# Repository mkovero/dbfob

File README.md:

# dbfob

**A dirt-cheap keyfob that tells you how loud it is — and how long your ears can take it.**

Double-click the button, look at the colour. Green means you're fine. Red means leave.

dbfob is an open-hardware sound level indicator sized for a keyring. It exists because nobody pulls out a phone on a dark dance floor to run a sound level meter, but everybody can glance at an LED. It is meant to be cheap enough that a venue, a festival or a hearing-health campaign can hand them out at the door next to the free earplugs.

> **Disclaimer:** dbfob is a hobby project, not a calibrated sound level meter or a medical device. Its readings and dose estimates can be wrong, so don't rely on it to protect your hearing. Use your own judgement: if it feels loud, wear earplugs or step away. If you're worried about your hearing, see a professional.

## Status

**Rev A prototype: boards up and measuring. Calibration at loud levels is not done yet. Rev B (B1, an AAA stick with NFC) arrived 2026-11-26 and its first board passes bring-up.**

| Part | State |
|---|---|
| [Hardware](hardware/README.md) | 5 assembled boards from JLCPCB, arrived 2026-10-12. Three are running, with no assembly faults so far. Standby measures 8.2 µA ([bring-up log](hardware/README.md#bring-up-log)). |
| [Firmware](firmware/README.md) | Spot check and dosimeter both work: PDM capture, A-weighting, LAeq, dose, and a flash log of the last dosimeter run (40 % CPU, no overruns). At about 61 dBA it reads within 0.5 dB of a consumer meter. The quiet-room floor is about 48 dBA, which doesn't matter for the bands. |
| [Case](hardware/case/README.md) | Two-shell case, in SLA and FDM builds. The FDM build is printed; a fit check with a board is due this week. |
| [Rev B board B1](hardware/b1/README.md) | 5 assembled boards from JLCPCB, arrived 2026-11-26: a 10.5 × 78.5 mm stick with one AAA cell on the back, a boost converter, a CH32L103, a new mic and an NFC tag. Board 1 passes every block tested so far ([bring-up](hardware/b1/README.md#bring-up)): it runs and starts from 0.57 V, Standby is 19 µA at 1.5 V, the button wakes it, the mic hears, and a phone reads the tag from a couple of centimetres once the antenna is trimmed (22 pF). It has only bring-up test firmware, the metering firmware is not ported yet. Not done: the cell contacts (it has run from a bench supply only), the wake by a phone tap, supply ripple, boards 2–5, a case. |

Next steps: confirm a full 12 h dosimeter night, then calibrate at 85–105 dBA against a reference meter. On rev B: fit the cell contacts, finish the bring-up and port the firmware. See [Next](#next).

## How it works

1. Double-click the button. The fob wakes from standby. A single press, such as one in a pocket, is ignored.
2. A PDM MEMS microphone samples the room for 3 seconds. Meanwhile the LED bar fills up, so you know the press registered and when the answer is coming.
3. The firmware A-weights the signal and computes the equivalent continuous level (LAeq).
4. A four-LED bar shows two verdicts for 2 seconds: a steady LED for a bare ear and a blinking LED for ear plugs. See below.

The LEDs are deliberately dim, since clubs are dark, and they auto-dim using one LED as a light sensor. The light thresholds are not tuned yet. Each reading is also printed on a UART pad for calibration.

### Colour bands

The bands are **levels at the ear**, not safety guarantees. The times are the full daily allowance at that level under the NIOSH / EU occupational curve, `T = 8 h × 2^((85 − L)/3)`: 85 dBA for 8 hours, 3 dB exchange rate.

| Colour | At the ear (dBA) | Daily allowance at that level |
|---|---|---|
| Green | ≤ 83 | Below the 85 dBA / 8 h limit |
| Yellow | 84–90 | About 10 h down to 2.5 h |
| Orange | 91–96 | About 2 h down to 40 min |
| Red | ≥ 97 | Under about 30 min |

A 3-second spot reading describes the room right now, not your night. The allowance is for a whole day starting from zero, so anything you've already heard today uses part of it. Green means this level is below the limit, not that the whole night is safe.

### Two LEDs, two questions

Every reading answers two questions at once, so there is no mode to set or forget:

- **Steady LED: what reaches a bare ear.** This is the room level itself: measured, with no assumptions.
- **Blinking LED: what would reach the ear through plugs that really give 12 dB.** This is a conditional estimate, not a measurement and not a safety verdict. The fob cannot know how well your plugs fit. Foam plugs claim 30+ dB on the box, but inserted in a hurry by someone who's had a drink, 10–15 dB is realistic. A badly seated plug can give much less. Individual fit testing is the only way to know your own attenuation, and NIOSH recommends it.

In a 100 dBA room, red glows steady and yellow blinks: you're in the red, and well-fitted plugs could bring you to yellow. When both answers are the same, only one steady LED lights.

The obvious alternative was a mode switch, but either default misleads someone. Assume plugs, and people without them get a falsely reassuring answer. Assume no plugs, and people who do wear them always see red, so the device looks useless to the people doing the right thing. Showing both removes the default, and the gap between the two LEDs is itself the argument for plugs.

### Modes

- **Double click — spot check.** Measures the current level and shows a colour for a few seconds. This is the mode that is always trustworthy, because you are holding the device out in front of you.
- **Long press (2 s) — dosimeter.** *Works on the bench. A 9 h run averaged 165 µA at 3.0 V: about 2 mAh per 12 h night, or roughly 80 nights on a CR2032. The first full 12 h runs, ending in auto-off, are in progress.*
  - **Start:** the LEDs light up and flash twice to confirm.
  - **While running:** the fob wakes about every 30 s and samples for 1 s about once a minute, with the LEDs off.
  - **Triple click:** shows the dose so far, bare ear, as a share of the daily allowance. The whole bar blinks for 3 s, and the faster it blinks, the more of the allowance is used: once a second at 0 %, twice a second at 50 %, and steadily lit at 100 %. A single click does nothing, so a press in a pocket doesn't light the fob.

  - **Stop:** another long press. The bar empties from red to green.
  - **Auto-off:** after 12 h it stops by itself. A triple click still shows the final dose until the next start.
  - **Double click:** a spot check, which works as usual while the dosimeter runs.
  - **Log:** the latest run, with about one level per minute, stays in flash after the cell is removed. You can read it later through the programmer with `make dose-log` (see [firmware/README.md](firmware/README.md)).

The catch is that a keyfob lives in a pocket. A pocket reads 10–20 dB low with the high end rolled off, so a dose collected in a pocket is a comforting lie. The dosimeter doesn't yet detect this. It would need to from the spectrum, since the high-band to low-band energy ratio collapses in a pocket, and then refuse to count those samples and flag the dose as incomplete. For now, clip it to your shoulder or a bag strap, with the mic port uncovered.

#### Example night

This is the flash log from one fob over a full 12 h run that ended in auto-off. The fob took 643 samples, all valid. It read with `make dose-log`, and the graph was drawn with `tools/dose_log.py --svg`:

- **Quiet room, 0–2.3 h:** the fob reads its own floor, about 48 dBA.
- **Music, 2.3–6.3 h:** 55–75 dBA. Hours of this barely move the dose.
- **Drums, 6.4 h:** ten minutes at 85–89.5 dBA. That alone takes the dose from about 0.5 % to 2.9 %, because each 3 dB doubles the rate.
- **Walk home, 9.8 h:** up to 80 dBA, with the fob in a pocket. Street noise would have read louder in the open, so this part of the dose is understated: the pocket problem described above.
- **Total:** LAeq 68.1 dBA over 12 h, which is 3.1 % of the daily allowance. A triple click would have shown the slowest blink, about once a second.

A cased and a bare fob side by side through a night in front of a big PA: [docs/logs/2026-10-31-case-ab.md](docs/logs/2026-10-31-case-ab.md).

## Hardware

This section describes rev A. Rev B's parts are in [hardware/b1](hardware/b1/README.md).

No radio, no display, no app. The design goal was **under €2 all-in**. The rev A parts come to about $1.85 per board at 1,000 units. A 130 dB-capable mic alone is about €1.2, so sub-€1 is out unless mic prices drop.

| Block | Part | Why |
|---|---|---|
| Microphone | Infineon **IM69D130**, PDM | **Acoustic overload ≥ 130 dB SPL.** Hobby-favourite digital mics clip at about 120 dB, which a club sub stack exceeds. It is digital, with ±1 dB sensitivity, so a batch can be calibrated rather than each unit, and the reading doesn't drift with battery voltage. |
| MCU | WCH **CH32V003F4P6** | The CH32V002/V006 are pin-compatible drop-ins, but were out of stock. The V003 has no hardware multiplier (handled in firmware) and needs at least 2.7 V. |
| LEDs | 4 × 0603 low-Vf LEDs as a bar: yellow-green, yellow, orange, red | InGaN green and blue LEDs need about 3 V and fade on a coin cell. The bar position also encodes the level for colour-blind users. D4 doubles as the light sensor. |
| Power | CR2032 in a Keystone 3034 | Standby measures 8.2 µA, so an idle fob lasts about 3 years. The mic is powered only while measuring. The dosimeter averages about 165 µA. |
| Input | 1 × tactile switch | Wakes the MCU. |
| Case | 3D-printed two-part shell, one M2 screw | Mic and LEDs at one end, keyring at the other. |

Background and trade-offs:
- The part comparison is in [docs/mic-mcu-options.md](docs/mic-mcu-options.md).
- An independent hardware audit, with the response to each finding, is in [docs/hardware-audit-2026-09-27.md](docs/hardware-audit-2026-09-27.md).

### Accuracy

Cheap MEMS parts are ±3 dB sensitivity; better ones are ±1 dB and factory-calibrated. Either is fine for four colour bands. The real uncertainty in this device is placement (held out vs. cupped in a hand vs. in a pocket) and earplug fit, not the microphone. Design effort goes into making "not trustworthy" visible, not into the last dB.

### Calibration

A 94 dB pistonphone won't couple to a MEMS port. Calibrate by substitution instead: place the fob next to a measurement mic in a room with pink noise at a few levels, note the offset, store it in flash. Also characterise the offset when hand-held vs. on a table, since that is how people will actually use it.

## Repository layout

```
hardware/        KiCad project, generated from the tables in hardware/tools/ (schematic, PCB, JLC outputs)
hardware/case/   FreeCAD case script, STEP/STL for printing, board geometry it is built from
hardware/b1/     rev B board (AAA stick, CH32L103, NFC tag): KiCad project, JLC outputs, bring-up log
firmware/        CH32V003 firmware on ch32fun: PDM capture, A-weighting, LAeq, LEDs, standby, dosimeter and its
                 flash log (tools/dose_log.py decodes it); host tests
firmware/b1-*/   rev B bring-up tests for the CH32L103: b1-test (LEDs, button, supply, tag, mic),
                 b1-standby (sleep current), b1-fd (wake by a phone's field)
docs/            part selection, hardware audit, log readout ideas
```

## Next

- [x] First bring-up: power, programming, mic capture, CPU load.
- [x] Standby current (8.2 µA) and the dosimeter current profile.
- [ ] VDD reference trim, light-sense thresholds. See [firmware/README.md](firmware/README.md#bring-up-checklist).
- [ ] Calibrate against a reference meter at 85–105 dBA, in the case: the level offset and the hand-held offset. So far it has only been compared with a consumer meter at about 61 dBA.
- [ ] Qualify the battery: the supply voltage under load across cell charge and temperature, then set the cutoff. At 2.8 V the sample wakes read 25 % more current than at 3.0 V. Re-measure on a range with a smaller burden voltage. A low-battery lockout (2.75 V) now keeps a tired cell from hanging the V003; test it with real cells. Wakes peak at over 10 mA with the LEDs on, which is hard on a CR2032.
- [x] Print the case.
- [ ] Check the printed case: the tolerances, the button flexure and the mic seal.
- [ ] A calibration procedure anyone can repeat with a known-good meter.
- [x] Rev B board designed and ordered: [B1](hardware/b1/README.md), an AAA stick with a boost converter, a CH32L103 (hardware multiplier, runs from 1.8 V), a mic port at the tip and an NFC tag for reading the dose log without a programmer ([directions, checked facts, experiments](docs/rev-b.md); [readout ideas](docs/log-readout.md)).
- [x] Rev B first bring-up on board 1: power from 0.57 V, programming, LEDs, button, Standby (19 µA at 1.5 V), mic, tag and antenna trim ([log](hardware/b1/README.md#bring-up)).
- [ ] Rev B: fit the cell contacts and run from a real AAA; wake by a phone tap; supply ripple at the mic; bring up boards 2–5.
- [ ] Rev B: port the metering firmware to the CH32L103 and the new mic, and write the log to the tag. Full-band A-weighting to 20 kHz is the goal there: rev A stops at 11.7 kHz, which reads only ~0.2–0.9 dB low on broadband noise, but high-frequency content is exactly what a listener stops noticing after a few drinks at a club ([band limit](firmware/README.md#signal-chain)).
- [ ] Rev B: a case for the stick.
- [ ] Dosimeter: confirm the 12 h auto-off and the flash log over a full night, then occlusion (pocket) detection.
- [ ] Get a batch into a venue and see if people use them.

## Non-goals

- Bluetooth, apps, logging to the cloud. The point is that nothing needs to be looked at except one LED.
- Certified measurement accuracy. This is a warning light, not a Class 1 meter.

## Why

Hearing damage is cumulative and irreversible, and the people most at risk are the ones who go out the most. Earplugs are cheap and effective, but people don't put them in unless they have a reason to. A colour that says "you are in the red" is a reason.

## License

Hardware: CERN-OHL-P. Firmware: MIT. Documentation: CC BY 4.0.

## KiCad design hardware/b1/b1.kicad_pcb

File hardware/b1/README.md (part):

# B1 (rev B)

A stick, 10.5 × 78.5 × 1.6 mm, 4 layers, with the mic at the tip and one AAA cell on the back: rev A's metering, with the log readable by tapping a phone. Scope and part choices are in [docs/rev-b.md](../../docs/rev-b.md#b1-stick-aaa-instead-of-cr2032-decided-2026-11-09).

**Status: boards arrived 2026-11-26; board 1 passes bring-up as far as it can go without cell contacts** (see [Bring-up](#bring-up)): supply, MCU, LEDs, button, Standby, mic, and the tag read by a phone after a 22 pF trim. Open: the contacts, FD wake, ripple, boards 2–5. Ordered from JLCPCB on 2026-11-16 (commit e3a0548: 5 boards, 4 layers, 1.6 mm, ENIG, Economic PCBA on the top side, mic SPH0655LM4H-1). Redrawn as the AAA stick on 2026-11-09. The first draft (2026-11-03) was a 30 × 26 mm CR2032 board. The [NFC test board](../nfc-test/README.md) shares its antenna, outline and cell but was dropped from the order on 2026-11-12: B1 finds its own trim (see [On the bench](#on-the-bench-nfc)).

## What's on it

Along the stick from the tip:

- **The tip, 24 mm:** the NFC coil, from [../lib/antenna.py](../lib/antenna.py), shared with the (unordered) test board. It has 9 turns of 0.15 mm track with a 0.15 mm gap, about 2.25 µH in air (NXP AN11276). The mic MK1 sits inside it, with its port through the board, and C6/R8 sit beside it. The coil's inner end meets LB at net tie NT1; LB crosses under the turns on B.Cu.
- **Just past the coil:** the tag U1, trim pads C1/C2 and C3.
- **The middle:** the tag's pull-ups, the LED bar (LED at the top edge, its resistor below, with only the cathode bar in silk; D1 and D2 are 0805, D3 and D4 0603, all four columns on one 1.75 mm pitch, LEDs in one row and resistors in another; the pull-ups and C3 stand 1.05 mm from the tag's body, JLC's spacing for a QFN), then the button SW1 about mid-stick (x 42.3 of 78.5), where a thumb finds it while the far end rests in the hand. Then the Tag-Connect footprint J1, **pads on the back**, under the cell, so a sweaty thumb can't touch them; its guide and clip holes go through the board in the gap between the two contacts' base pads. Then the MCU U2, still in that gap, so its vias have room all round, and right after it the boost converter U3, with L1 over it and C5 under it, so the switching and output loops stay on F.Cu (hand-drawn). It sits over the + contact's base pad: its VCELL via goes into that pad, the rest of its vias above and below it.
- **The far end:** a 2.4 mm round ring hole H1 in the corner, past the + contact's plate, for hanging the stick up. The MY-AAA-07 drawing has no dimension for the plate; scaled from it, the plate's top lip stands 1.4 mm inboard of the foot's tip, which puts it at x 74.2 to 74.5 depending on where the contact sits on its pads, with about 0.4 mm of scaling and part tolerance on top. The hole starts at x 75.2 and is as big as the corner allows: 0.9 mm of web to the end and to the side, 0.72 mm to the contact's foot pad (a hole counts as board edge). The board is 2 mm longer than the first B1 draft to make room. Solder the + contact towards the mic end of its pads, and check the gap with a real one. The board's name is on the back silk, under the coil.
- **Back:** the AAA cell between two MYOUNG MY-AAA-07 spring contacts, hand-fitted, + towards the far end. Other nets' vias keep at least 0.35 mm from the contacts' pads (the pads are grown while routing), so hand-soldering has room. Everything past the coil sits under the cell.
- **No planes or pours on any layer.** Copper near the loop detunes it, so GND is tracks. Every layer under the coil is kept clear, apart from a band at its cell end where LB and the mic's nets cross under the turns.

**Why 4 layers:** two would not route in 10.5 mm. The MCU's fan-out, the tag's lines and the mic's lines share one corridor, and the contacts' pads fill the middle of B.Cu. The inner layers carry signals only.

| Ref | What | Note |
|---|---|---|
| U2 | CH32L103F8U6, C22467836 | QFN-20 3 × 3. No NRST pin, BOOT0 tied low inside |
| U3 | TLV61220DBVR, C111811 | boost, 0.7 V start-up, 3.0 V out (R9 1 MΩ / R10 200 kΩ); EN to the cell, always on |
| L1 | MPL2016S4R7MHT, C98335 | 4.7 µH, 2.0 × 1.6 mm, multilayer |
| C5, C7 | 10 µF | boost output, input |
| MK1 | Knowles SPH0655LM4H-1, C22376158 | 132.5 dB SPL AOP, −37 ±1 dBFS, normal mode 1.1–4.8 MHz (below 0.9 MHz it drops to low-power mode, 116 dB AOP: keep the clock at 1.5 MHz). 0.6 mm port (NPTH) through the board, inside the coil. Replaces the IM66D130M, which JLC assembles only as Standard PCBA |
| R8, C6 | 100 Ω, 1 µF (C15849) | mic supply from PA4, filtered against the boost's burst ripple |
| U1 | NT3H2111W0FHKH, C710403 | NTAG I2C plus 1k, powered from PB14 |
| C1, C2 | 0603 trim, **not fitted** | C0G, value found on the bench: 22 pF in C1 on board 1 (see Bring-up) |
| C3, C4 | 100 nF | tag and MCU decoupling |
| R1, R2 | 4.7 kΩ, 0402 (C25900) | SDA / SCL pull-ups to NFC_VCC. 0402 to make room for the 0805 LEDs |
| R3 | 100 kΩ, 0402 (C25741) | FD pull-up to VDD |
| R11 | 4.7 kΩ, 0402 (C25900) | in series with PA7's cell sense |
| D1–D4, R4–R7 | green KT-0805G (C2297), yellow KT-0805Y (C2296), red KT-0603R (C2286) ×2; 1 kΩ, 2.2 kΩ ×3 | **All JLC basic parts** (no extended fee), which is why the bar is green, yellow, red, red: basic has no orange, and green and yellow only in 0805. The green is InGaN (2.6–3.1 V at 5 mA) on the 3.0 V rail: dim by design, tune R4 on the bench. Each on its own hardware PWM channel; D4's cathode on PA10 for ambient-light sensing. D3's net is still called LED_O |
| SW1 | TS-1187A, C318884 | measure button, PA0/WKUP to VDD: no resistor |
| BT1 | 2 × MY-AAA-07 (C6937109) | **hand-fit on the back**, so JLC assembly stays one-sided |
| H1 | 2.4 mm NPTH | ring / cord hole in the far corner; a light split ring is fine, but a heavy key bunch should hang from the case |
| J1 | Tag-Connect TC2050-IDC footprint (KiCad stock `TC2050-IDC-FP`, for the legged plug), no part | 2 × 5 pogo pads at 1.27 mm, 3 guide holes and 4 clip holes (2.4 mm), **on the back**, along the stick between the button and the MCU, its holes in the gap between the contacts' base pads, 0.4 mm clear of the button's body on the front, where the clips latch. ARM Cortex 10-pin pinout: 1 VDD (VTref), 2 SWDIO, 4 SWCLK, 6 TX (SWO slot: the dB stream), 3/5/9 GND; 7, 8, 10 not connected (no NRST pin) |

**MCU pins** (full table in `tools/gen_sch.py`):

| Pin | Net | | Pin | Net |
|---|---|---|---|---|
| 1 PA0 | BTN (WKUP: wakes Standby on a rising edge) | | 7 PA7 | VCELL (ADC7: the cell, for the low-battery lockout) |
| 2 PA1 | LED_O (TIM2_CH2) | | 8 PB0 | FD (EXTI) |
| 3 PA2 | LED_Y (TIM2_CH3) | | 9 PB10 | SCL (I2C2) |
| 4 PA3 | LED_G (TIM2_CH4) | | 10 PB11 | SDA (I2C2) |
| 14 PA8 | LED_R (TIM1_CH1) | | 12 PB14 | NFC_VCC |
| 18 PA10 | LED_R_K | | 15 PA9 | TX (USART1) |
| 5 PA4 | MIC_PWR (through R8 to MIC_VDD) | | 17 PA13 | SWDIO |
| 6 PA5 | MIC_CLK (SPI1 SCK) | | 16 PA14 | SWCLK |
| 20 PA6 | MIC_DATA (SPI1 MISO) | | 11, 13 | spare (PB13, PB15) |

- **Button on WKUP.** With EWUP set, PA0 is forced to an input with pull-down in Standby, so the button goes to VDD and needs no resistor. Not PB13: it shares a pad with PB6 = CC1, and some lots force CC1's 5.1 kΩ pull-down on in Standby (datasheet table 3-8-1 note 3). For the same reason NFC_VCC is on PB14, not PB13.
- Pins sharing a pad inside the chip (PB1/PB10, PA10/PB7, PA11/PA13, PA12/PA14): only one of each pair may drive. Keep CC2_PD off, or PA10 gets 5.1 kΩ to ground.
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
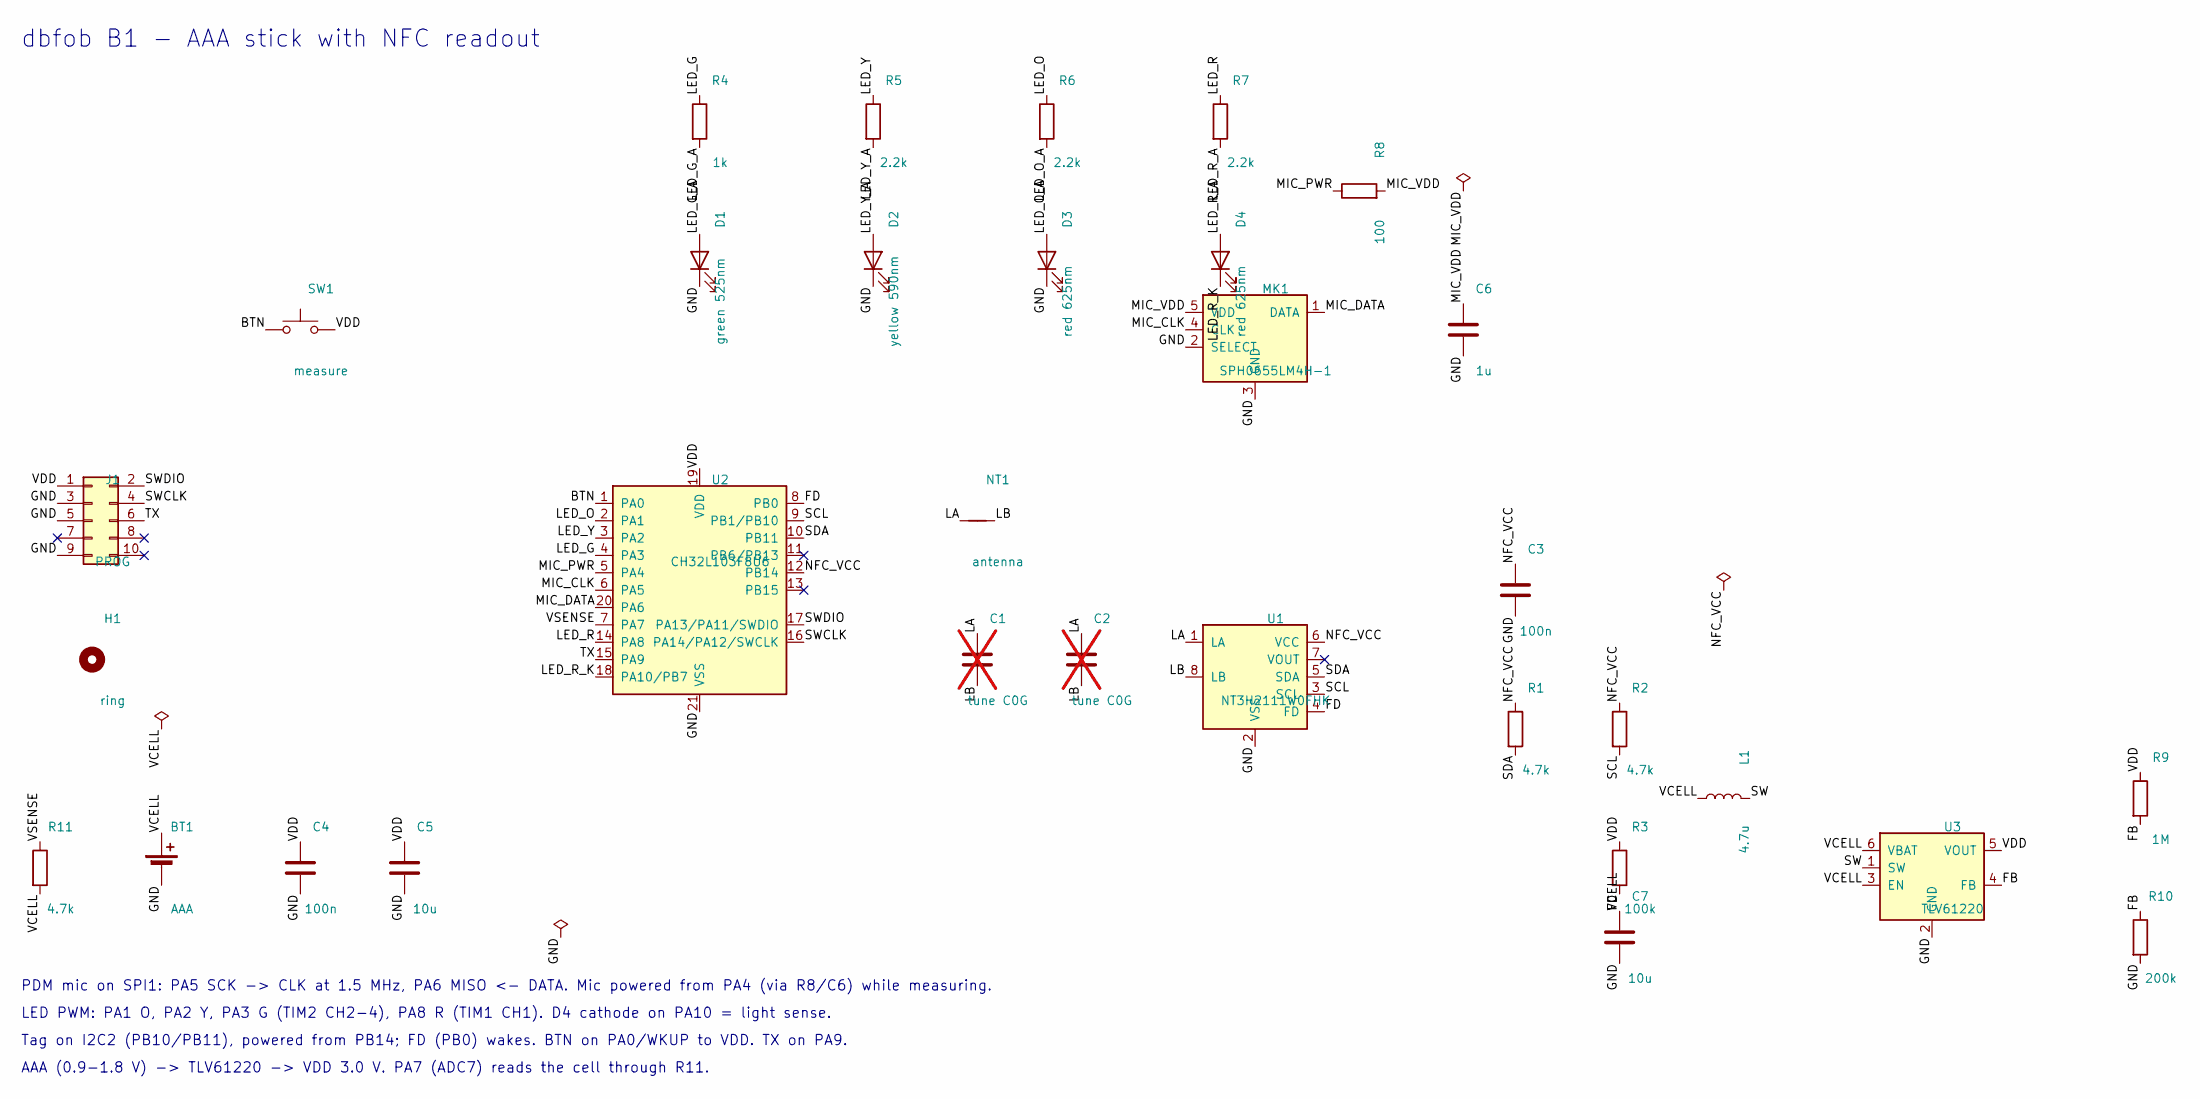
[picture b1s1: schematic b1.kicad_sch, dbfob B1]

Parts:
BT1: AAA; BatteryContacts_MYOUNG_MY-AAA-07_1xAAA; MPN MY-AAA-07
C1, C2: tune C0G; C_0603_1608Metric; not fitted
C3, C4: 100n; C_0603_1608Metric; MPN CC0603KRX7R9BB104; LCSC C14663
C5, C7: 10u; C_0603_1608Metric; MPN CL10A106KP8NNNC; LCSC C19702
C6: 1u; C_0603_1608Metric; MPN CL10A105KB8NNNC; LCSC C15849
D1: green 525nm; LED_0805_2012Metric_narrow; MPN KT-0805G; LCSC C2297
D2: yellow 590nm; LED_0805_2012Metric_narrow; MPN KT-0805Y; LCSC C2296
D3, D4: red 625nm; LED_0603_1608Metric; MPN KT-0603R; LCSC C2286
H1: ring; RingHole_2.4mm
J1: PROG; Tag-Connect_TC2050-IDC-FP_2x05_P1.27mm_Vertical
L1: 4.7u; L_0806_2016Metric_MPL2016; MPN MPL2016S4R7MHT; LCSC C98335
MK1: SPH0655LM4H-1; Knowles_SPH0655LM4H_LGA-5_3.5x2.65mm; MPN SPH0655LM4H-1-8; LCSC C22376158
NT1: antenna; NetTie-2_SMD_Pad0.5mm
R1, R2, R11: 4.7k; R_0402_1005Metric; MPN 0402WGF4701TCE; LCSC C25900
R3: 100k; R_0402_1005Metric; MPN 0402WGF1003TCE; LCSC C25741
R4: 1k; R_0603_1608Metric; LCSC C21190
R5, R6, R7: 2.2k; R_0603_1608Metric; LCSC C4190
R8: 100; R_0603_1608Metric; MPN 0603WAF1000T5E; LCSC C22775
R9: 1M; R_0603_1608Metric; MPN 0603WAF1004T5E; LCSC C22935
R10: 200k; R_0603_1608Metric; MPN 0603WAF2003T5E; LCSC C25811
SW1: measure; SW_Push_1P1T_XKB_TS-1187A; MPN TS-1187A-B-A-B; LCSC C318884
U1: NT3H2111W0FHK; NXP_XQFN-8_1.6x1.6mm_P0.5mm; MPN NT3H2111W0FHKH; LCSC C710403
U2: CH32L103F8U6; UQFN-20-1EP_3x3mm_P0.4mm_EP1.85x1.85mm; MPN CH32L103F8U6; LCSC C22467836
U3: TLV61220; SOT-23-6; MPN TLV61220DBVR; LCSC C111811

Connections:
/BTN: SW1.1, U2.1 (PA0)
/FB: R9.2, R10.1, U3.4 (FB)
/FD: R3.2, U1.4 (FD), U2.8 (PB0)
/GND: BT1.2 (-), C3.2, C4.2, C5.2, C6.2, C7.2, D1.1 (K), D2.1 (K), D3.1 (K), J1.3, J1.5, J1.9, MK1.2 (SELECT), MK1.3 (GND), R10.2, U1.2 (VSS), U2.21 (VSS), U3.2 (GND)
/LA: C1.1, C2.1, NT1.1, U1.1 (LA)
/LB: C1.2, C2.2, NT1.2, U1.8 (LB)
/LED_G: R4.1, U2.4 (PA3)
/LED_G_A: D1.2 (A), R4.2
/LED_O: R6.1, U2.2 (PA1)
/LED_O_A: D3.2 (A), R6.2
/LED_R: R7.1, U2.14 (PA8)
/LED_R_A: D4.2 (A), R7.2
/LED_R_K: D4.1 (K), U2.18 (PA10/PB7)
/LED_Y: R5.1, U2.3 (PA2)
/LED_Y_A: D2.2 (A), R5.2
/MIC_CLK: MK1.4 (CLK), U2.6 (PA5)
/MIC_DATA: MK1.1 (DATA), U2.20 (PA6)
/MIC_PWR: R8.1, U2.5 (PA4)
/MIC_VDD: C6.1, MK1.5 (VDD), R8.2
/NFC_VCC: C3.1, R1.1, R2.1, U1.6 (VCC), U2.12 (PB14)
/SCL: R2.2, U1.3 (SCL), U2.9 (PB1/PB10)
/SDA: R1.2, U1.5 (SDA), U2.10 (PB11)
/SW: L1.2, U3.1 (SW)
/SWCLK: J1.4, U2.16 (PA14/PA12/SWCLK)
/SWDIO: J1.2, U2.17 (PA13/PA11/SWDIO)
/TX: J1.6, U2.15 (PA9)
/VCELL: BT1.1 (+), C7.1, L1.1, R11.2, U3.3 (EN), U3.6 (VBAT)
/VDD: C4.1, C5.1, J1.1, R3.1, R9.1, SW1.2, U2.19 (VDD), U3.5 (VOUT)
/VSENSE: R11.1, U2.7 (PA7)

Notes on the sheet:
dbfob B1 - AAA stick with NFC readout
PDM mic on SPI1: PA5 SCK -> CLK at 1.5 MHz, PA6 MISO <- DATA. Mic powered from PA4 (via R8/C6) while measuring.
LED PWM: PA1 O, PA2 Y, PA3 G (TIM2 CH2-4), PA8 R (TIM1 CH1). D4 cathode on PA10 = light sense.
Tag on I2C2 (PB10/PB11), powered from PB14; FD (PB0) wakes. BTN on PA0/WKUP to VDD. TX on PA9.
AAA (0.9-1.8 V) -> TLV61220 -> VDD 3.0 V. PA7 (ADC7) reads the cell through R11.

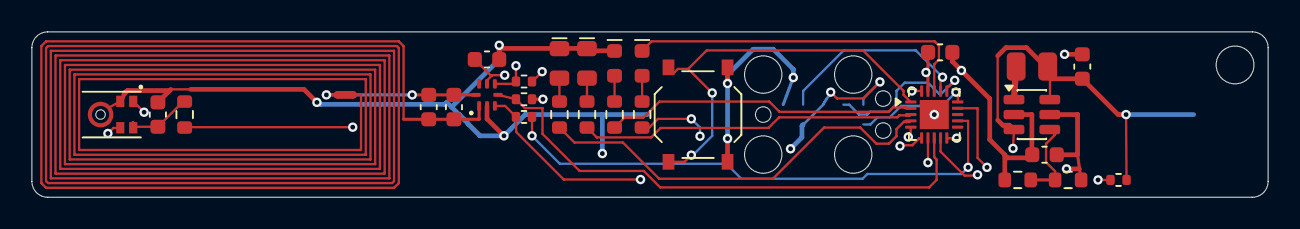
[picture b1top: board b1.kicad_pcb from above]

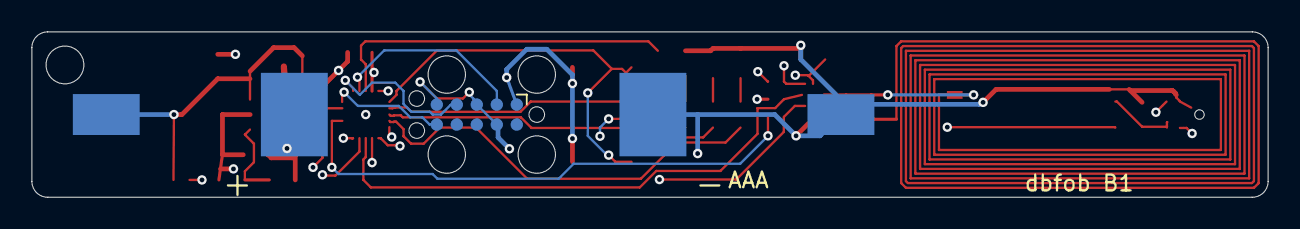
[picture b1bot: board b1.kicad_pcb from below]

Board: 4 copper layers, 78.5 x 10.5 mm, 32 parts (2 on the bottom side), 29 nets.

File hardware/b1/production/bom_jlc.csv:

Comment,Designator,Footprint,LCSC Part #
100n CC0603KRX7R9BB104,"C3,C4",C_0603_1608Metric,C14663
10u CL10A106KP8NNNC,"C5,C7",C_0603_1608Metric,C19702
1u CL10A105KB8NNNC,C6,C_0603_1608Metric,C15849
green 525nm KT-0805G,D1,LED_0805_2012Metric_narrow,C2297
yellow 590nm KT-0805Y,D2,LED_0805_2012Metric_narrow,C2296
red 625nm KT-0603R,"D3,D4",LED_0603_1608Metric,C2286
4.7u MPL2016S4R7MHT,L1,L_0806_2016Metric_MPL2016,C98335
SPH0655LM4H-1 SPH0655LM4H-1-8,MK1,Knowles_SPH0655LM4H_LGA-5_3.5x2.65mm,C22376158
4.7k 0402WGF4701TCE,"R1,R2,R11",R_0402_1005Metric,C25900
100k 0402WGF1003TCE,R3,R_0402_1005Metric,C25741
1k,R4,R_0603_1608Metric,C21190
2.2k,"R5,R6,R7",R_0603_1608Metric,C4190
100 0603WAF1000T5E,R8,R_0603_1608Metric,C22775
1M 0603WAF1004T5E,R9,R_0603_1608Metric,C22935
200k 0603WAF2003T5E,R10,R_0603_1608Metric,C25811
measure TS-1187A-B-A-B,SW1,SW_Push_1P1T_XKB_TS-1187A,C318884
NT3H2111W0FHK NT3H2111W0FHKH,U1,NXP_XQFN-8_1.6x1.6mm_P0.5mm,C710403
CH32L103F8U6 CH32L103F8U6,U2,UQFN-20-1EP_3x3mm_P0.4mm_EP1.85x1.85mm,C22467836
TLV61220 TLV61220DBVR,U3,SOT-23-6,C111811

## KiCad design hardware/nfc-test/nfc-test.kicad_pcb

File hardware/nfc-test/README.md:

# NFC test board (for rev B / B1)

**Dropped on 2026-11-12, not ordered.** Shipped in the same order as B1 it could not steer B1's layout, and B1 answers the same question itself: its tag runs from the phone's field with no firmware, over the same antenna and cell, with its own mic and lines in place (see [B1's bench steps](../b1/README.md#on-the-bench-nfc)). Kept as a draft; it still imports [../lib/antenna.py](../lib/antenna.py) but its board files are not regenerated when that changes.

10.5 × 94 mm as drawn (B1 is now 76.5 mm; rerun make_pcb if this board is ever revived), 1.0 mm thick, 4 layers like B1 (the inner two are empty here, so the coil sees the same stack-up): B1's stick outline. It answers one question before B1 is trusted: **does B1's NFC antenna read on a phone with the AAA cell beside it, and with what trim?** This is [experiment 4](../../docs/rev-b.md#experiments-before-any-board).

It goes in the **same order as B1**, so it can't steer B1's layout. B1 copies this antenna and its trim pads exactly. Whatever trim value this board finds goes straight onto B1's pads.

## What's on it

- **Tip, 24 mm:** B1's antenna block, from [../lib/antenna.py](../lib/antenna.py), which both boards import so they can't drift apart:
  - a 9-turn PCB coil, 0.15 mm track with a 0.15 mm gap, about 23 × 9.3 mm, about 2.25 µH in air (NXP AN11276 formula);
  - its inner end meets LB through net tie NT1; LB drops through a via and crosses under the cell-end turns on B.Cu to the tag;
  - **U1** (NT3H2111, NTAG I2C plus 1k), **C3** and the **C1/C2** trim pads (not fitted) just past the coil, where they sit on B1.
- **Back:** B1's AAA cell between two MYOUNG MY-AAA-07 spring contacts, its near end about 1.4 mm past the coil. The cell is there for its steel can. At 1.5 V it can't run the tag (1.67 V minimum) or the LED.
- **Past the tag:** the pull-ups where B1 has them, the D1 field LED, and six host pads.

| Ref | What | Note |
|---|---|---|
| U1 | NT3H2111W0FHKH, C710403 | VOUT unused |
| C1, C2 | 0603 trim, **not fitted** | C0G, chosen on the bench |
| C3 | 100 nF | VCC decoupling |
| R1, R2 | 4.7 kΩ | SDA / SCL pull-ups to VCC |
| R3 | 10 kΩ | FD pull-up to VCC |
| R4, D1 | 1 kΩ, red | lit while a reader's field is on and VCC is up: FD pulls it low |
| BT1 | 2 × MY-AAA-07 (C6937109) | **hand-fit on the back**, so JLC assembly stays one-sided |
| J1 | 6 SMD pads, 2.54 mm | `G C F D V B` = GND, SCL, FD, SDA, VCC, VCELL; for wires or pogo pins |

## Regenerate

```sh
python3 hardware/lib/gen_lib.py               # NT3H2111 symbol, XQFN8 + AAA contact footprints
python3 hardware/nfc-test/tools/gen_sch.py    # tables -> schematic
python3 hardware/nfc-test/tools/make_pcb.py   # coil + placement + hand-drawn LA/LB, the router does the rest
python3 hardware/nfc-test/tools/fab.py        # -> production/
```

This follows the same procedure as rev A ([../README.md](../README.md)).

**How the antenna is drawn.** The coil is LA track; its outer end runs straight to the tag's LA pin. Its inner end meets LB through net tie NT1, and LB crosses under the turns on B.Cu (VI to VO). DRC doesn't check clearance within one net, so `antenna.py` builds the turns at a fixed pitch and asserts the 0.15 mm gap, and the vias' gap to the turns, itself.

**State at commit:**
- **ERC:** clean, apart from the library-table warnings.
- **DRC:** 0 errors, 0 unconnected, 0 parity issues.
- **Repeatability:** two runs give byte-identical boards.
- **CPL:** all 7 placements checked against JLC's EasyEDA footprints.

## On the bench

Power the tag side from a 3 V supply on V and G (or a host MCU, which also gets C, D and F) so D1 can show the field.

1. **No cell.** Tap with an Android (NXP TagInfo) and an iPhone. Write a URL with NFC Tools. Note the read distance, and the distance at which D1 lights.
2. **Find the resonance**, if a NanoVNA and a small pickup loop are at hand. Couple the loop loosely and read the S11 dip, f0. Then the trim is **C = 50 pF × ((f0 / 13.56 MHz)² − 1)**. Without a VNA, try 0, 4.7, 10, 15 and 22 pF C0G in C1, and keep the value with the longest read distance.
3. **Fit the cell** (an alkaline and, if B1 will take one, a lithium AAA). Repeat steps 1–2. This shows how much the cell costs.
4. **In the case**, if one is printed: repeat steps 1–2 with the board in it.
5. **Locked iPhone:** with the screen on, a tap should open the URL with no app.

Record f0, the trim value, the read distance and the LED distance for each step. The trim value from step 3 (or 4) goes on B1's pads.

**Why the coil is under 2.75 µH.** 13.56 MHz needs 2.75 µH with the tag's 50 pF (44–56 pF). The coil is short of that on purpose: the cell, its contacts and a phone pull the tuning about, and a parallel trim cap can only pull the resonance down.

**What it doesn't copy.** The coil, LA/LB, tag, trim pads, outline, stack-up and cell are B1's exactly. B1's Tag-Connect footprint (about 18 mm from the coil), MCU and boost converter, and its mic and lines are not: the mic's lid sits inside the coil, with two 11 mm tracks beside it, a 12 mm GND track under it, and four more nets crossing under the turns at the cell end. The cell's steel can is the bigger effect, but check B1's resonance again (VNA, step 2) before its C1/C2 value is final.

**Ordering note:** In1 and In2 are empty on purpose (same stack-up as B1). JLC may ask about blank inner layers on a 4-layer order: confirm.

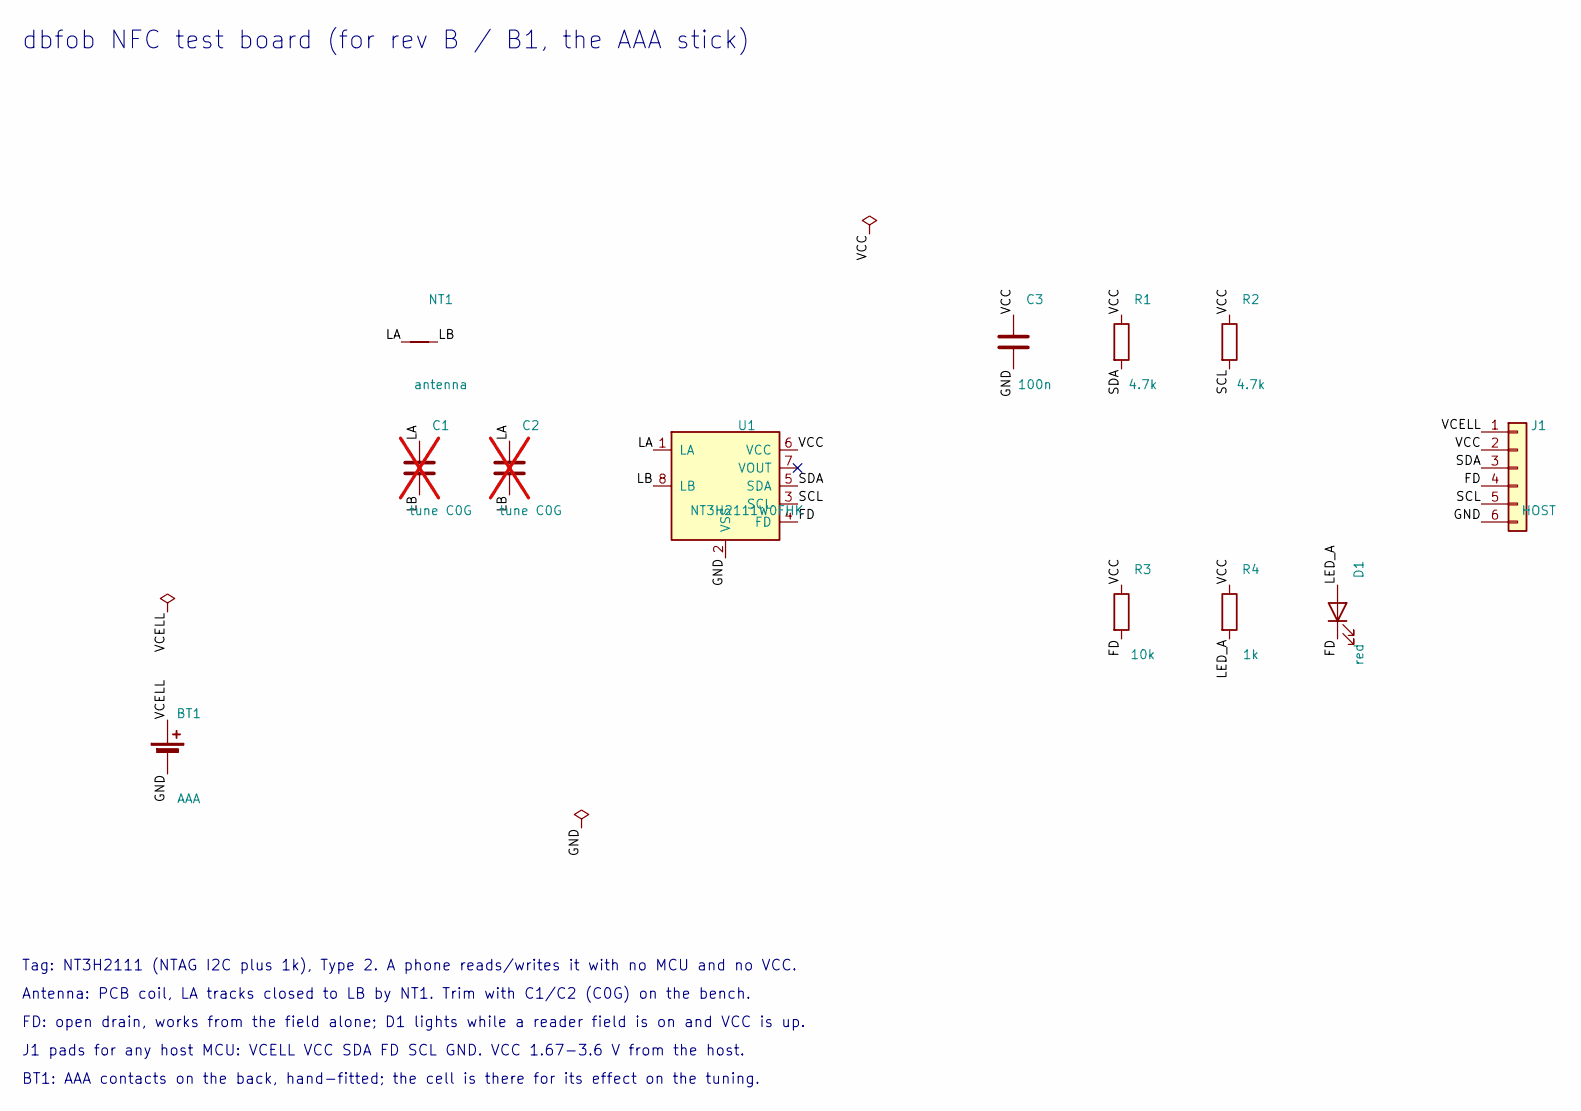
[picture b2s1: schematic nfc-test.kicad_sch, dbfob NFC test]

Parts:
BT1: AAA; BatteryContacts_MYOUNG_MY-AAA-07_1xAAA; MPN MY-AAA-07
C1, C2: tune C0G; C_0603_1608Metric; not fitted
C3: 100n; C_0603_1608Metric; MPN CC0603KRX7R9BB104; LCSC C14663
D1: red; LED_0603_1608Metric; MPN KT-0603R; LCSC C2286
J1: HOST; TestPads_1x06_P2.54mm_D1.2mm
NT1: antenna; NetTie-2_SMD_Pad0.5mm
R1, R2: 4.7k; R_0603_1608Metric; MPN 0603WAF4701T5E; LCSC C23162
R3: 10k; R_0603_1608Metric; MPN 0603WAF1002T5E; LCSC C25804
R4: 1k; R_0603_1608Metric; MPN 0603WAF1001T5E; LCSC C21190
U1: NT3H2111W0FHK; NXP_XQFN-8_1.6x1.6mm_P0.5mm; MPN NT3H2111W0FHKH; LCSC C710403

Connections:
/FD: D1.1 (K), J1.4, R3.2, U1.4 (FD)
/GND: BT1.2 (-), C3.2, J1.6, U1.2 (VSS)
/LA: C1.1, C2.1, NT1.1, U1.1 (LA)
/LB: C1.2, C2.2, NT1.2, U1.8 (LB)
/LED_A: D1.2 (A), R4.2
/SCL: J1.5, R2.2, U1.3 (SCL)
/SDA: J1.3, R1.2, U1.5 (SDA)
/VCC: C3.1, J1.2, R1.1, R2.1, R3.1, R4.1, U1.6 (VCC)
/VCELL: BT1.1 (+), J1.1

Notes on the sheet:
dbfob NFC test board (for rev B / B1, the AAA stick)
Tag: NT3H2111 (NTAG I2C plus 1k), Type 2. A phone reads/writes it with no MCU and no VCC.
Antenna: PCB coil, LA tracks closed to LB by NT1. Trim with C1/C2 (C0G) on the bench.
FD: open drain, works from the field alone; D1 lights while a reader field is on and VCC is up.
J1 pads for any host MCU: VCELL VCC SDA FD SCL GND. VCC 1.67-3.6 V from the host.
BT1: AAA contacts on the back, hand-fitted; the cell is there for its effect on the tuning.

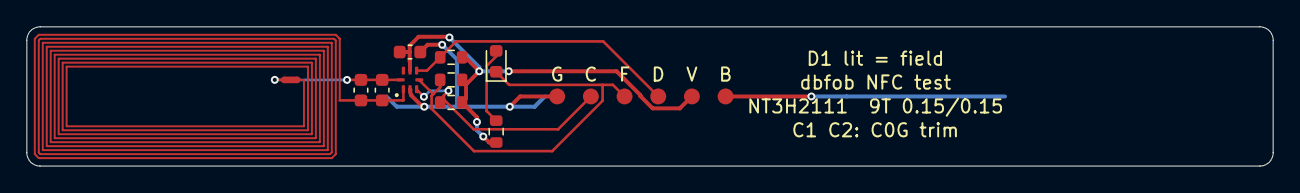
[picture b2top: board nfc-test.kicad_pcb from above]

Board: 4 copper layers, 94.0 x 10.5 mm, 12 parts (1 on the bottom side), 9 nets.

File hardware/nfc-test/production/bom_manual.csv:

Designator,Value,MPN,Footprint,Note
BT1,AAA,MY-AAA-07,BatteryContacts_MYOUNG_MY-AAA-07_1xAAA,hand-fit on the back: 2x MYOUNG MY-AAA-07 (LCSC C6937109)
"C1,C2",tune C0G,,C_0603_1608Metric,"not fitted: antenna trim, C0G, chosen on the bench,not fitted: second trim position"
J1,HOST,,TestPads_1x06_P2.54mm_D1.2mm,"SMD pads for wires or pogo pins: 1 VCELL, 2 VCC, 3 SDA, 4 FD, 5 SCL, 6 GND"

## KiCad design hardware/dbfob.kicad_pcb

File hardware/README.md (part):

# dbfob hardware, rev A

30 × 52.5 mm, 2 layers, all parts on the top side. It is powered by a CR2032, the only input is one button, and the only output is a four-LED bar. Part choices are explained in [../docs/mic-mcu-options.md](../docs/mic-mcu-options.md).

## Everything regenerates

The procedure follows `studer-vca/etofab.md`. The tables in `tools/gen_sch.py` are the only source; do not hand-edit the sheet or the board.

```sh
python3 hardware/tools/gen_sch.py    # tables -> dbfob.kicad_sch
python3 hardware/tools/make_pcb.py   # schematic -> placed, routed, poured, DRC'd board (~30 s)
python3 hardware/tools/fab.py        # board -> production/
```

These need KiCad 10 (`kicad-cli` and the `pcbnew` Python module) and [KiCadRoutingTools](https://github.com/drandyhaas/KiCadRoutingTools) at `/home/mui/src/KicadRoutingTools` (override with `KRT=`).

State at commit:
- **ERC:** clean, apart from KiCad's library-table warnings and one expected `pin_to_pin` warning. That warning comes from the PWR_FLAG on MIC_VDD, which is powered by a GPIO.
- **DRC:** 0 errors, 0 warnings, 0 unconnected, 0 schematic-parity issues.
- **Reproducibility:** two runs give byte-identical boards.

## Circuit

| U1 pin | Port | Net | Function |
|---|---|---|---|
| 15 | PC5 | MIC_CLK | SPI1 SCK, the PDM clock: 1.5 MHz (see [clock plan](#pdm-clock-plan)) |
| 17 | PC7 | MIC_DATA | SPI1 MISO, the PDM data. MK1 SELECT is tied to GND |
| 16 | PC6 | MIC_VDD | GPIO push-pull. The mic is powered only while measuring (≈0.6 mA at 1.5 MHz). Discard audio until 50 ms after VDD *and* the clock are both running |
| 20 | PD3 | LED_G | TIM2_CH2, D1 yellow-green |
| 19 | PD2 | LED_Y | TIM1_CH1, D2 yellow |
| 14 | PC4 | LED_O | TIM1_CH4, D3 orange |
| 13 | PC3 | LED_R | TIM1_CH3, D4 red (anode side) |
| 12 | PC2 | LED_R_K | D4 cathode: drive low to light it; reverse-bias and time the decay to sense ambient light |
| 10 | PC0 | BTN | SW1 to GND. Use the internal pull-up; EXTI wakes the MCU from standby |
| 18 | PD1 | SWIO | Programming (WCH-LinkE) |
| 2 | PD5 | TX | USART1 TX: prints dB readings during calibration |

**LEDs.** The bar is deliberately dim: a club is dark and the fob should not light up the room. The resistors cap the current at about 0.45 mA (2.2 kΩ), or about 1 mA for the dimmer yellow-green (1 kΩ). Firmware uses PWM to go well below that indoors and shows the result for about 2 s.
- **Ambient light sensing.** D4's cathode is on PC2 rather than GND, so the red LED doubles as a light sensor. Reverse-bias it (PC3 low, PC2 high), switch PC2 to input, and time how long it takes to read low. Fast means bright, which lets the firmware tell a dark room from daylight.
- **Why these LEDs.** All four are low-Vf AlInGaP/GaP types (1.6–2.6 V), so every colour still lights near the end of the cell's life; InGaN green and blue LEDs need about 3 V.
- **Order.** The bar runs G Y · O R from left to right. The position of the lit LED also encodes the level, so the bar works for colour-blind users.

**J1** is four 2.54 mm pads: `+ D G T` = VBAT, SWIO, GND, TX. Fit a header by hand, or hold pogo pins against it. It is not assembled.

**Mic port.** MK1 is a bottom-port mic, so it hears through the 0.8 mm hole to the **back** of the board (marked MIC). Don't cover it, and give the case an opening there.

**Coin cell.** The Keystone 3034 uses a PCB pad as the − contact. The cell's + can wraps around onto the − face at the rim, so the top layer has no copper in the ring under the rim: only solder mask would stand between + and a GND pour. The − pad reaches ground through four vias inside the pad. There is no reverse-polarity protection; the holder only accepts the cell one way round.

## MCU: fitted with a CH32V003

The CH32V002 and CH32V006 had **zero stock at JLC/LCSC on 2026-09-27**, so the BOM carries the pin-compatible **CH32V003F4P6** (C5187096, 1035 in stock). The TSSOP-20 pinout is identical: it was checked against table 2-1 of the V002 datasheet. When stock returns, change the LCSC number in `gen_sch.py`. The board stays the same.

The V003 costs the project two things:
- **No hardware multiply.** Build the firmware for `rv32ec`, which runs on all three chips. The biquads cost more cycles but fit easily at 48 MHz.
- **Minimum supply of 2.7 V instead of 2.0 V.** How much of the cell that costs is **not known yet**. See [Power](#power-unqualified).

## PDM clock plan

The IM69D130 is specified only in four clock bands: 0.40–0.95, 1.05–1.9, 2.1–2.65 and 2.9–3.3 MHz (datasheet table 4). The CH32's SPI clock is its bus clock divided by a power of two, 2 to 256. The earlier plan of 1.024 MHz fell between two bands and could not be generated anyway.

The plan is **1.5 MHz**: 48 MHz / 32, or 24 MHz / 16 if the core runs at 24 MHz to save current. Decimating by 64 gives **23,437.5 samples/s**, so the audio bandwidth reaches about 11.7 kHz. The decimator and the A-weighting biquads are designed for exactly that rate. The mic's startup time (20 ms to ±0.5 dB, 50 ms to ±0.2 dB) counts from when both VDD and the clock are present (table 5).

Still to show on hardware: the V003 has no multiplier and 2 KB of RAM, so it must keep up with 1.5 Mbit/s of PDM continuously.

## Power (unqualified)

These were datasheet estimates. Measured values for board 1 are in the [bring-up log](#bring-up-log).

- **Active.** The CH32V003 draws about 4–6 mA at 48 MHz (HSI), and the mic about 0.6 mA. A CR2032's internal resistance rises as it discharges and as it gets cold. With 50 Ω, 6 mA pulls a 3.0 V cell down to the V003's 2.7 V minimum, and the 10 µF cap bridges that for only about half a millisecond, not a 3 s measurement. The V003 can also run below its guaranteed range before its reset threshold trips.
  - Firmware runs the measurement at 24 MHz, and measures VDD under load against the internal reference throughout.
  - Below a cutoff with margin, it shows an explicit **invalid / battery** pattern instead of a level.
  - Qualification: log minimum VDD through acquisition and display, across cell state of charge and temperature, with real cells.
  - If usable capacity is too low, reconsider the MCU or supply in rev B.
- **Standby.** The V003's typical standby current is 7.6 µA (LSI off), about 67 mAh per year. That limits an idle fob to roughly 3 years on a 220 mAh cell, much more than self-discharge does. The CH32V002 would be worse, at 17.5 µA. The mic uses no standby current because it is unpowered. If shelf life matters, rev B could add a button-triggered power latch, so standby becomes a switch's leakage.

## Programming

J1 pin 1 is wired directly to the cell's + terminal. **Take the cell out before connecting a programmer or powering a board for calibration.** A WCH-LinkE supplying 3.3 V into an installed CR2032 would charge it, and Energizer allows 1 µA of reverse current at most. Put the cell back in afterwards. The legend on the back of the board says the same. A fixture should enforce this order, for example by physically blocking the holder. A board powered from its cell must be programmed with the programmer's supply pin unconnected.

## Ordering at JLCPCB

Upload `production/dbfob-gerbers.zip`, then for assembly `production/bom_jlc.csv` and `production/cpl_jlc.csv`.

- **PCB:** 2 layers, 1.6 mm, any colour, tented vias.
- **Finish: lead-free HASL for prototypes, ENIG for production.** At 5 boards ENIG took the PCBA order from €6.46 to €22 (2026-09-27) for little gain here. The mic's 0.45 mm pads on a 0.7 mm pitch solder fine on HASL, and the holder's spring presses the cell onto the slightly domed − pad. Choose lead-free rather than leaded HASL: these get carried on keyrings. At volume the ENIG premium per board shrinks, and its flat, non-oxidising battery contact becomes worth it.
- **Assembly:** economic, top side only, 15 placements, 12 BOM lines. J1 is not placed. Board cleaning: no.
- **Tooling holes.** On a 1×1 board without edge rails, JLC drills its tooling holes into the board itself, and ground copper covers almost all of both sides. In the placement review, check they stay clear of:
  - the cell's − pad and the copper-free ring around it,
  - the traces between the LEDs and U1,
  - the mic hole.

  If they don't, order a 1×1 panel with edge rails instead.
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
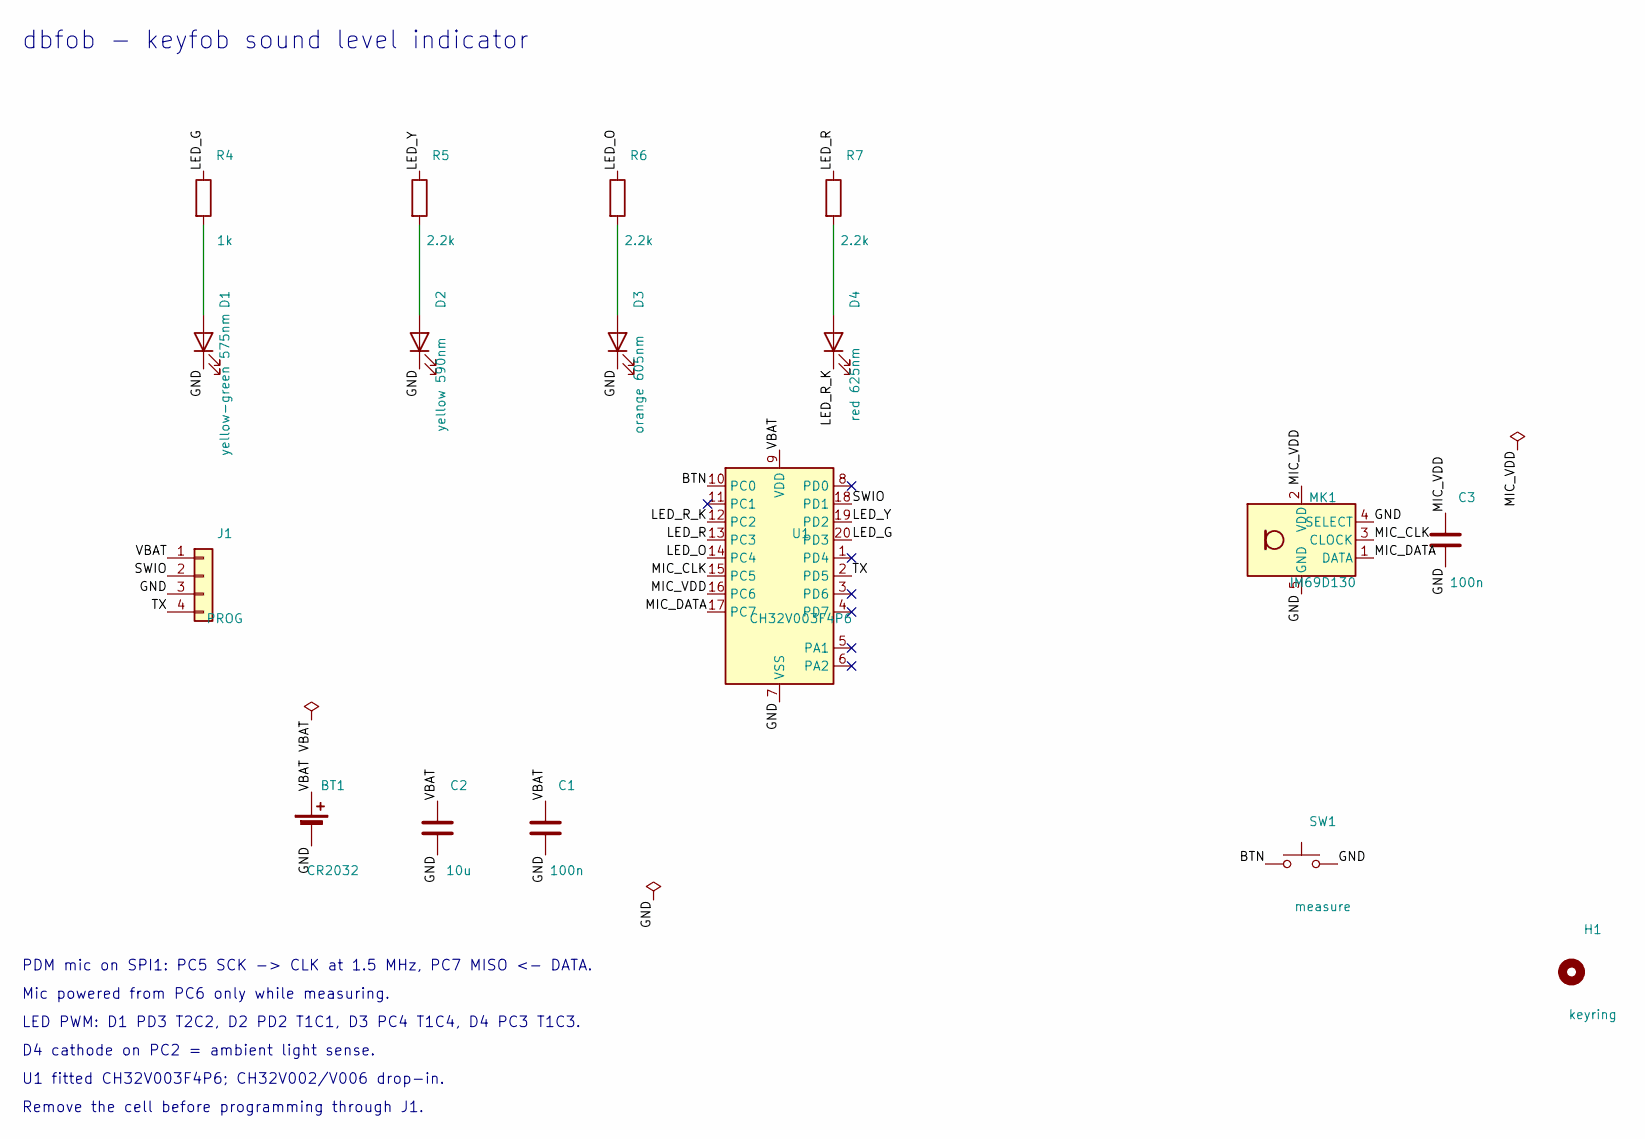
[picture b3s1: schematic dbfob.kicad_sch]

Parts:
BT1: CR2032; BatteryHolder_Keystone_3034_1x20mm; MPN Keystone 3034TR; LCSC C5213768
C1, C3: 100n; C_0603_1608Metric; MPN CC0603KRX7R9BB104; LCSC C14663
C2: 10u; C_0603_1608Metric; MPN CL10A106KP8NNNC; LCSC C19702
D1: yellow-green 575nm; LED_0603_1608Metric; MPN NCD0603C3; LCSC C89809
D2: yellow 590nm; LED_0603_1608Metric; MPN KT-0603Y; LCSC C2287
D3: orange 605nm; LED_0603_1608Metric; MPN KT-0603O; LCSC C111340
D4: red 625nm; LED_0603_1608Metric; MPN KT-0603R; LCSC C2286
H1: keyring; MountingHole_3.2mm_M3
J1: PROG; PinHeader_1x04_P2.54mm_Vertical
MK1: IM69D130; Infineon_PG-LLGA-5-1; MPN IM69D130V01XTSA1; LCSC C536262
R4: 1k; R_0603_1608Metric; LCSC C21190
R5, R6, R7: 2.2k; R_0603_1608Metric; LCSC C4190
SW1: measure; SW_Push_1P1T_XKB_TS-1187A; MPN TS-1187A-B-A-B; LCSC C318884
U1: CH32V003F4P6; TSSOP-20_4.4x6.5mm_P0.65mm; MPN CH32V003F4P6; LCSC C5187096

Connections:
/BTN: SW1.1, U1.10 (PC0)
/GND: BT1.2 (-), C1.2, C2.2, C3.2, D1.1 (K), D2.1 (K), D3.1 (K), J1.3, MK1.4 (SELECT), MK1.5 (GND), SW1.2, U1.7 (VSS)
/LED_G: R4.1, U1.20 (PD3)
/LED_O: R6.1, U1.14 (PC4)
/LED_R: R7.1, U1.13 (PC3)
/LED_R_K: D4.1 (K), U1.12 (PC2)
/LED_Y: R5.1, U1.19 (PD2)
/MIC_CLK: MK1.3 (CLOCK), U1.15 (PC5)
/MIC_DATA: MK1.1 (DATA), U1.17 (PC7)
/MIC_VDD: C3.1, MK1.2 (VDD), U1.16 (PC6)
/SWIO: J1.2, U1.18 (PD1)
/TX: J1.4, U1.2 (PD5)
/VBAT: BT1.1 (+), C1.1, C2.1, J1.1, U1.9 (VDD)
unnamed: D1.2 (A), R4.2
unnamed: D2.2 (A), R5.2
unnamed: D3.2 (A), R6.2
unnamed: D4.2 (A), R7.2

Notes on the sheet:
dbfob - keyfob sound level indicator
PDM mic on SPI1: PC5 SCK -> CLK at 1.5 MHz, PC7 MISO <- DATA.
Mic powered from PC6 only while measuring.
LED PWM: D1 PD3 T2C2, D2 PD2 T1C1, D3 PC4 T1C4, D4 PC3 T1C3.
D4 cathode on PC2 = ambient light sense.
U1 fitted CH32V003F4P6; CH32V002/V006 drop-in.
Remove the cell before programming through J1.

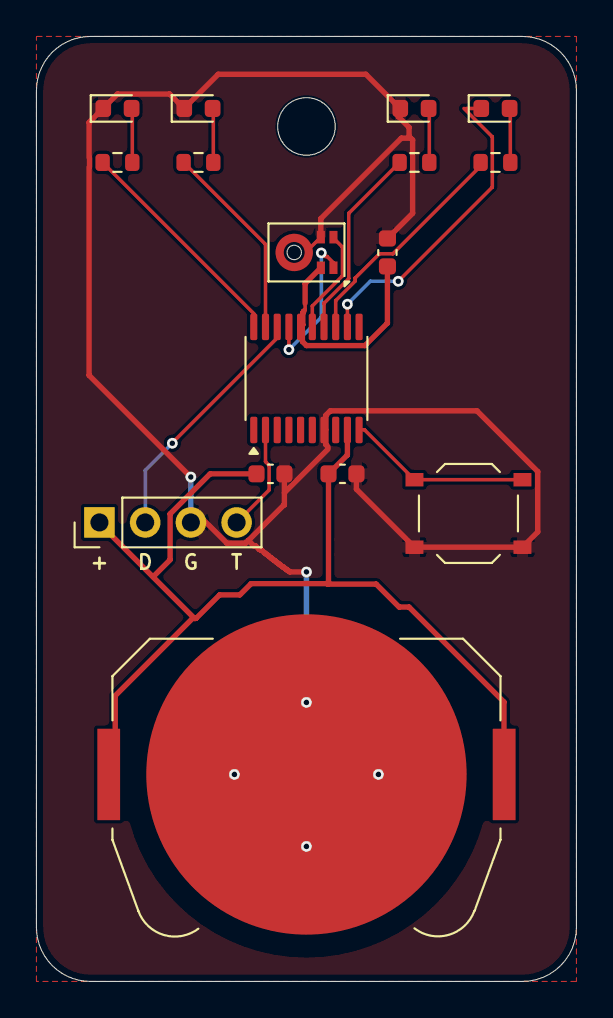
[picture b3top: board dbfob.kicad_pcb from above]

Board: 2 copper layers, 30.0 x 52.5 mm, 17 parts (0 on the bottom side), 17 nets.

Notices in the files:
hardware/dbfob.kicad_pcb:
dBA at ear  CERN-OHL-P
